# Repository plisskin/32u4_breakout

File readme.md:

# Atmega32U4 Breakout Board

This is a simple breakout board for the Atmega32U4 microcontroller.  It brings out all of the pins to headers and also provides places for a crystal resonator and an ICSP programming header.  

All of the power pins route to the top of the board where power can be connected in a single spot and all of the ground pins route to the bottom of the board where ground can be connected in a single spot.  The intention is to use jumpers to connect the power/ground pins to the power/ground 'header'.

Created using KiCad 8 and routed using freerouter.

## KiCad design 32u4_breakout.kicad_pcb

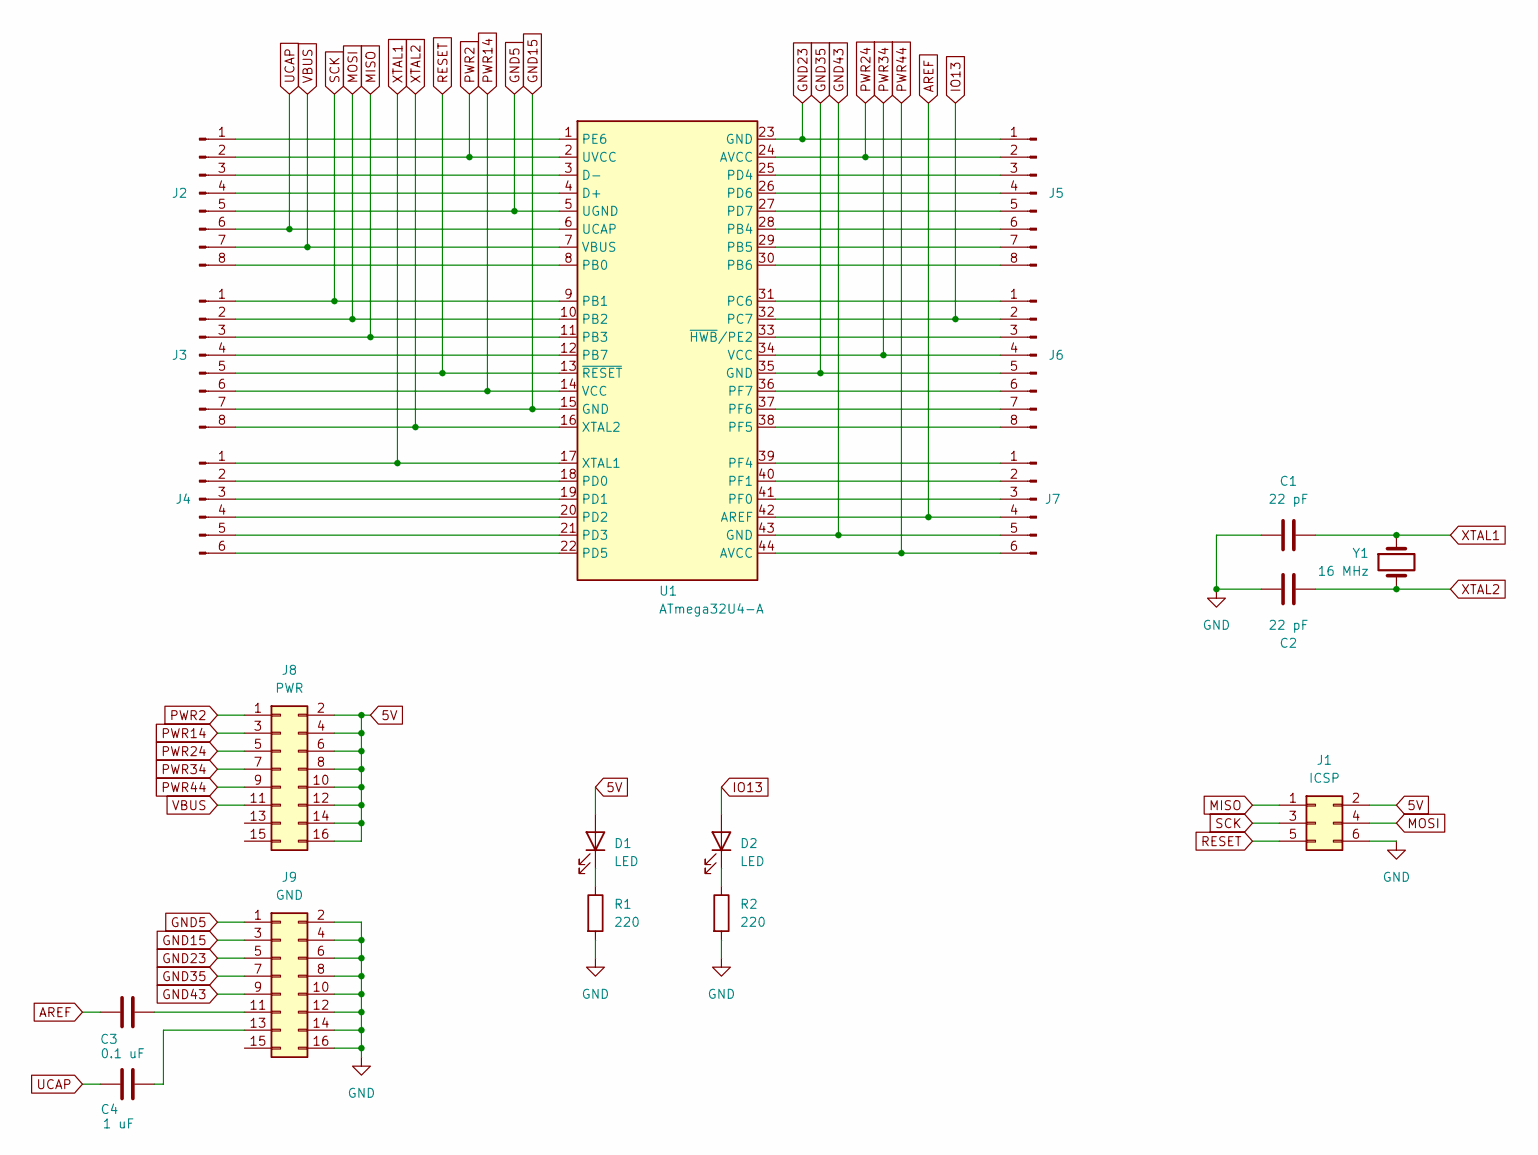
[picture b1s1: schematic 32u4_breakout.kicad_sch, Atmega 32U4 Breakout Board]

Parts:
C1, C2: 22 pF; C_1206_3216Metric; Manufacturer Part C1206C220J5GAC7800
C3: 0.1 uF; C_1206_3216Metric; Manufacturer Part C1206C104J5RAC7025
C4: 1 uF; C_1206_3216Metric; Manufacturer Part C1206C105K4RAC7800
D1, D2: LED; LED_1206_3216Metric
J1: ICSP; PinHeader_2x03_P2.54mm_Vertical; Manufacturer Part 0751020041
J2, J3, J5, J6: PinHeader_1x08_P2.54mm_Vertical
J4, J7: PinHeader_1x06_P2.54mm_Vertical
J8: PWR; PinHeader_2x08_P2.54mm_Vertical
J9: GND; PinHeader_2x08_P2.54mm_Vertical
R1, R2: 220; R_1206_3216Metric
U1: ATmega32U4-A; TQFP-44_10x10mm_P0.8mm; Manufacturer Part ATMEGA32U4-AU
Y1: 16 MHz; Crystal_SMD_HC49-SD; Manufacturer Part 830034122

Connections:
5V: D1.2 (A), J1.2, J8.2, J8.4, J8.6, J8.8, J8.10, J8.12, J8.14, J8.16
AREF: C3.1, J7.4, U1.42 (AREF)
GND: C1.2, C2.2, J1.6, J9.2, J9.4, J9.6, J9.8, J9.10, J9.12, J9.14, J9.16, R1.2, R2.2
GND5: J2.5, J9.1, U1.5 (UGND)
GND15: J3.7, J9.3, U1.15 (GND)
GND23: J5.1, J9.5, U1.23 (GND)
GND35: J6.5, J9.7, U1.35 (GND)
GND43: J7.5, J9.9, U1.43 (GND)
IO13: D2.2 (A), J6.2, U1.32 (PC7)
MISO: J1.1, J3.3, U1.11 (PB3)
MOSI: J1.4, J3.2, U1.10 (PB2)
unnamed: D1.1 (K), R1.1
unnamed: D2.1 (K), R2.1
unnamed: J2.1, U1.1 (PE6)
unnamed: J2.3, U1.3 (D-)
unnamed: J2.4, U1.4 (D+)
unnamed: J2.8, U1.8 (PB0)
unnamed: J3.4, U1.12 (PB7)
unnamed: J4.2, U1.18 (PD0)
unnamed: J4.3, U1.19 (PD1)
unnamed: J4.4, U1.20 (PD2)
unnamed: J4.5, U1.21 (PD3)
unnamed: J4.6, U1.22 (PD5)
unnamed: J5.3, U1.25 (PD4)
unnamed: J5.4, U1.26 (PD6)
unnamed: J5.5, U1.27 (PD7)
unnamed: J5.6, U1.28 (PB4)
unnamed: J5.7, U1.29 (PB5)
unnamed: J5.8, U1.30 (PB6)
unnamed: J6.1, U1.31 (PC6)
unnamed: J6.3, U1.33 (~HWB/PE2)
unnamed: J6.6, U1.36 (PF7)
unnamed: J6.7, U1.37 (PF6)
unnamed: J6.8, U1.38 (PF5)
unnamed: J7.1, U1.39 (PF4)
unnamed: J7.2, U1.40 (PF1)
unnamed: J7.3, U1.41 (PF0)
unnamed: C3.2, J9.11
unnamed: C4.1, J9.13
PWR2: J2.2, J8.1, U1.2 (UVCC)
PWR14: J3.6, J8.3, U1.14 (VCC)
PWR24: J5.2, J8.5, U1.24 (AVCC)
PWR34: J6.4, J8.7, U1.34 (VCC)
PWR44: J7.6, J8.9, U1.44 (AVCC)
RESET: J1.5, J3.5, U1.13 (~RESET)
SCK: J1.3, J3.1, U1.9 (PB1)
UCAP: C4.2, J2.6, U1.6 (UCAP)
VBUS: J2.7, J8.11, U1.7 (VBUS)
XTAL1: C1.1, J4.1, U1.17 (XTAL1), Y1.1
XTAL2: C2.1, J3.8, U1.16 (XTAL2), Y1.2

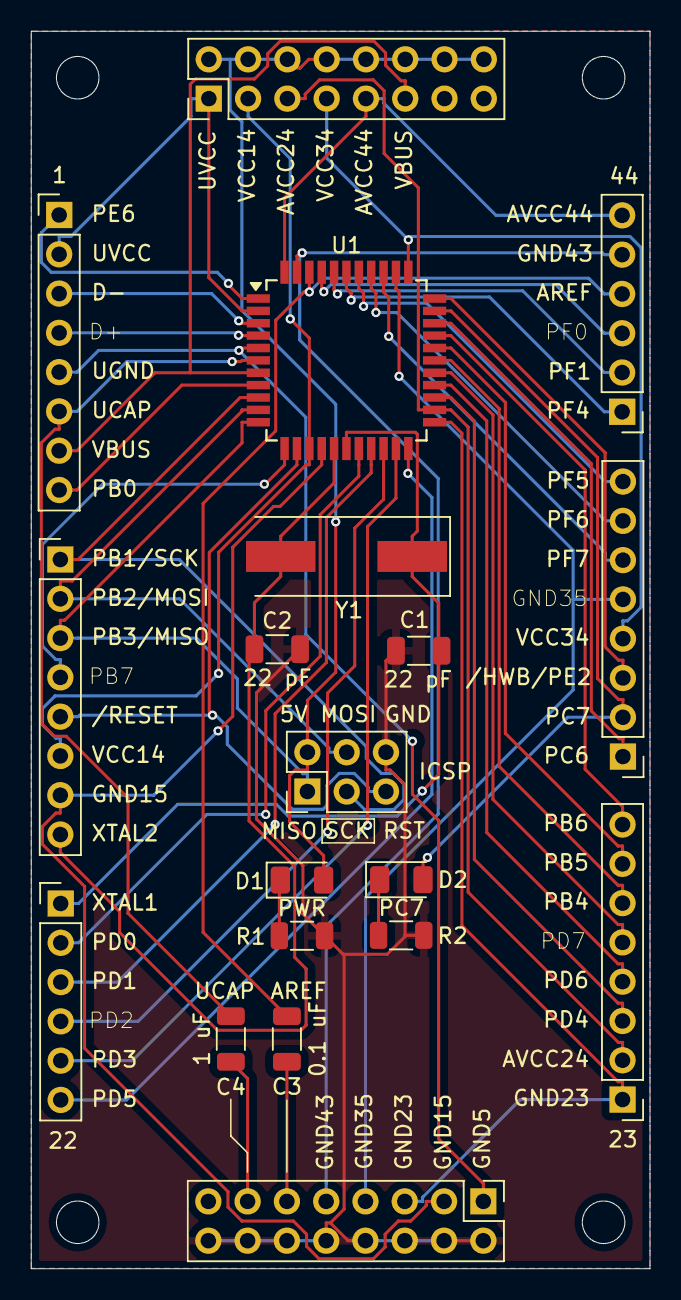
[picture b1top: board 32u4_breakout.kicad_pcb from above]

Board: 2 copper layers, 40.0 x 80.0 mm, 19 parts (0 on the bottom side), 50 nets.

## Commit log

2024-07-23 Added LED for power and PC7/IO13
2024-08-15 Added pcb picture to readme.md
2024-10-15 Fixed routing (missing grounds)
